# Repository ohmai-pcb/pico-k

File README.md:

<!-- SPDX-License-Identifier: CERN-OHL-P-2.0 -->
<!-- Copyright 2026 The OhmAI contributors -->
# 🌡️ pico-k — RP2350A + MAX31856 Type-K Thermocouple Board

**A 51 × 21 mm Raspberry Pi Pico 2 drop-in board with an integrated 19-bit Type-K thermocouple front end — built end-to-end as the v0.1 dogfood showcase for [OhmAI](https://github.com/ohmai-pcb/ohmai).**

[**Honest Assessment & Grades**](#project-status--honest-assessment) · [**Design effort / AI usage (estimate)**](#design-effort--ai-usage-estimate) · [**Key Specifications**](#key-specifications-verified-against-bombomcsv) · [**On-Board Pin Map**](#on-board-pin-map-rp2350a-verified-against-hardwaregenpinmapyaml) · [**Repo Map & Checks**](#repository-map--running-checks) · [**Exceptions & Waivers**](#exceptions-and-waivers)

| 2D Routed Layout (`docs/layout/routed-2d.png`) | 3D Rendered Board (`docs/layout/routed-3d.png`) |
|---|---|
|  |  |

**Designed with [OhmAI](https://github.com/ohmai-pcb/ohmai).** Rev-A design, pre-fab: ERC and DRC are clean; the board has not been fabricated yet.

---

### What is `pico-k`?

`pico-k` is an open hardware reference project and the **v0.1 dogfood testbed** built to stress-test [OhmAI](https://github.com/ohmai-pcb/ohmai)'s 12-phase hardware engineering workflow, datasheet citation checks, 3-rule BOM sourcing, and independent review gates.

Every artifact in this repository — from requirements (`docs/requirements.md`), safety/compliance analysis (`docs/safety.md`), and page-cited component constraints (`parts/constraints/*.yaml`) to the 6-sheet hierarchical KiCad 9 schematic (`hardware/*.kicad_sch`), 4-layer routed PCB (`hardware/pico-k.kicad_pcb`), multi-source BOM (`bom/bom.csv`), and pre-board bring-up self-test (`test/firmware/bringup_selftest.py`) — was generated and verified through `ohmai` with a human owner reviewing and signing off at each gate.

### ✨ Hardware Highlights

- 🧠 **Raspberry Pi Pico 2 Core (`RP2350A`)** — Dual Cortex-M33 / Hazard3 MCU (`U1`, QFN-60 7×7 mm), **Winbond `W25Q32RVXHJQ`** 4 MB QSPI flash (`U2`, XSON-8 2×3 mm), **Abracon `ABM8-272-T3`** 12 MHz crystal (`Y1`), and internal 1.1 V DVDD buck inductor **MPS `MPL-AT2512-3R3`** (`L1`, 3.3 µH) following the *Hardware Design with RP2350* reference circuit.
- 🌡️ **19-Bit Cold-Junction-Compensated Type-K Front End (`MAX31856MUD+T`)** — Analog Devices `MAX31856` (`U5`, TSSOP-14) on `SPI1` (`GP12`–`GP15` via cuttable jumpers `JP1`–`JP4`; `DRDY` and `FAULT` on `TP11`/`TP12`), paired with top-mounted **Omega `PCC-SMD`** miniature flat-pin Type-K socket clips (`J2`, `J3`) and a differential/common-mode RC input filter (`R12`/`R13` 100 Ω, `C25`/`C26` 10 nF X7R, `C14` 100 nF X7R).
- ⚡ **Buck-Boost 3.3 V Power & Protected USB-C** — **TI `TPS63001DRCR`** (`U3`, VSON-10 3×3 mm) 3.3 V buck-boost regulator with **Murata `DFE201612P-2R2M`** 2.2 µH inductor (`L2`, 2016), 16-pin USB-C receptacle (`J1`), **STMicro `USBLC6-2SC6`** ESD array (`U4`, SOT-23-6), and **onsemi `MBR120VLSFT1G`** (`D1`, SOD-123FL) `VBUS`→`VSYS` Schottky diode.
- 📏 **Drop-In 51 × 21 mm Form Factor with Flat Bottom (`R-02`, `R-07`)** — 4-layer 1.0 mm FR-4 stackup (`F.Cu` / `In1.Cu` solid GND / `In2.Cu` 3V3 / `B.Cu`), single-sided top SMD assembly (`66` fitted parts across `36` BOM rows), and 40-pin Pico-compatible edge pinout (`J4`).

---

## Project Status & Honest Assessment

| Dimension | Grade | Honest Commentary |
|---|---|---|
| **1. End-to-End Autonomy** | **5.5 / 10** | **Human-steered, not hands-off, and not yet physically built.** The workflow produced a complete, rule-checked package from Phase 1 (`requirements`) through Phase 11 (`out/fab/rev-A/`) and Phase 12 pre-board preparation (`test/bringup-plan.md`, `test/firmware/bringup_selftest.py`, `docs/manual.md`). However, getting there required substantial human owner steering, course corrections, and tool fixes along the way (`D-001`–`D-030`, `docs/layout/retro.md`), and the board has **not yet been ordered or bench-tested** (`review:fab` and `review:bringup` remain open). |
| **2. Engineering Complexity / Skill Level** | **4.5 / 10** | **Reference-application complexity.** Electrically, this is a straightforward modification of a Raspberry Pi Pico 2 reference design combining three application circuits (`RP2350A` core, `TPS63001` buck-boost, and `MAX31856` SPI thermocouple front end) — low-to-moderate difficulty for an electronics engineer. Where the workflow added genuine rigor was in quantitative verification (exact datasheet page citations, DC-bias derating math, thermal/loop checks, and verified multi-source BOM alternates). |
| **3. PCB Routing & Layout Quality** | **5.0 / 10** | **DRC-clean (`0` violations, `0` unconnected), but visibly machine-routed.** Fitting 66 top-side SMD parts (including two large `PCC-SMD` thermocouple clips `J2`/`J3`) into 51 × 21 mm via `Freerouting` + scripted pass-completion (`hardware/gen/pcb/handroute.py`) produced meandering autorouter traces rather than clean human layout artistry. Closing the board required owner waivers for 25 short signal hops on the `In2.Cu` (`3V3`) plane (`D-020`/`D-023`, pour remains 1 piece with a 0.91 mm minimum neck), downsizing `C18`/`C27` to `0402` (`D-025`), and accepting stretched decoupler placement (`3.2–11.8 mm`) on several `RP2350A` supplies (`D-030`). Every compromise is listed in [Exceptions and waivers](#exceptions-and-waivers). |

---

## Key Specifications (Verified against `bom/bom.csv`)

| Subsystem | RefDes & MPNs (`bom/bom.csv`) | Reference / Decision |
|---|---|---|
| **MCU & Memory** | `U1` Raspberry Pi `RP2350A` (QFN-60 7×7, `C42411118`), `L1` MPS `MPL-AT2512-3R3` (3.3 µH DVDD buck inductor, `C3224274`), `U2` Winbond `W25Q32RVXHJQ` (4 MB QSPI flash, XSON-8 2×3, `C32246052`), `Y1` Abracon `ABM8-272-T3` (12 MHz crystal, SMD3225-4P, `C20625731`) with `C23`/`C24` 15 pF C0G (`C1548`) & `R3` 1 kΩ (`C11702`) | [`parts/constraints/RP2350A.yaml`](parts/constraints/RP2350A.yaml), `D-001`, `D-006`, `D-009` |
| **Thermocouple Front End** | `U5` Analog Devices `MAX31856MUD+T` (TSSOP-14, `C2653162`), `J2`/`J3` Omega `PCC-SMD` (2 × SMT flat-pin socket clips), `R12`/`R13` 100 Ω series (`0402WGF1000TCE`, `C25076`), `C25`/`C26` 10 nF 50 V X7R CM (`CL05B103KB5NNNC`, `C15195`), `C14` 100 nF 16 V X7R diff (`CL05B104KO5NNNC`, `C1525`), `C12`/`C13` 100 nF `AVDD`/`DVDD` decouplers | [`parts/constraints/MAX31856MUD+T.yaml`](parts/constraints/MAX31856MUD+T.yaml), `R-03`, `R-04`, `R-07`, `D-001`, `D-004` |
| **Power & USB Stage** | `U3` TI `TPS63001DRCR` (3.3 V buck-boost, VSON-10 3×3, `C28060`), `L2` Murata `DFE201612P-2R2M` (2.2 µH, 2016, `C79317`), `C20` Samsung `CL21A106KAYNNNE` (10 µF 25 V X5R, 0805, `C15850`), `C21`/`C22`/`C31` 3 × 10 µF 25 V X5R (`CL10A106MA8NRNC`, 0603, `C96446`), `J1` SHOU HAN `TYPE-C 16PIN 2MD(073)` (`C2765186`), `U4` STMicro `USBLC6-2SC6` (SOT-23-6 USB ESD, `C7519`), `D1` onsemi `MBR120VLSFT1G` (SOD-123FL Schottky, `C223608`) | [`parts/constraints/TPS63001DRCR.yaml`](parts/constraints/TPS63001DRCR.yaml), `D-004`, `D-006`, `D-030` |
| **Housekeeping & UI** | `SW1` XKB `TS-1187A-B-A-B` (`BOOTSEL` button, SMD 5.1×5.1, `C318884`) via `R4` 1 kΩ, `D2` KENTO `KT-0805G` (0805 green LED on `GP25`, `C2297`) via `R22` 470 Ω (`C25117`), `Q1` Diodes Inc. `DMG1012T-7` (SOT-523 N-MOSFET on `VSYS_SENSE`, `C20512`) with `R19` 20 kΩ / `R9` 10 kΩ divider | [`hardware/led_boot_adc.kicad_sch`](hardware/led_boot_adc.kicad_sch), `D-006`, `D-007` |
| **PCB Stackup & Form Factor** | **51.0 × 21.0 mm** (`R-02`), 4-layer 1.0 mm FR-4 (`F.Cu` / `In1.Cu` solid GND / `In2.Cu` 3V3 / `B.Cu`), ENIG (JLCPCB `JLC04101H-7628`), top-side SMD assembly (`R-07`), EU target market (`D-003`) | [`docs/requirements.md`](docs/requirements.md), `D-003`, `D-006`, `D-017` |

---

## On-Board Pin Map (`RP2350A`, verified against `hardware/gen/pinmap.yaml`)

| Signal / GPIO | Pin / Net Routing (`pinmap.yaml`) | On-Board Function |
|---|---|---|
| `GP12` (`SPI1_RX`) | `U1.16` / `J4.16` / `JP1` → `U5.11` (`TC_SDO`) | `MAX31856` `SDO` (SPI1 MISO via cuttable jumper `JP1`) |
| `GP13` (`SPI1_CSn`) | `U1.17` / `J4.17` / `JP2` → `U5.9` (`TC_CS`) | `MAX31856` `CS` (SPI1 CSN via `JP2`, 10 kΩ pull-up `R7` to `3V3`) |
| `GP14` (`SPI1_SCK`) | `U1.18` / `J4.19` / `JP3` → `U5.10` (`TC_SCK`) | `MAX31856` `SCLK` (SPI1 SCK via `JP3`) |
| `GP15` (`SPI1_TX`) | `U1.19` / `J4.20` / `JP4` → `U5.12` (`TC_SDI`) | `MAX31856` `SDI` (SPI1 MOSI via `JP4`) |
| `TC_DRDY` | `U5.7` / `TP11.1` (DNF 10 kΩ pull-up `R23`) | `MAX31856` active-low data-ready test pad `TP11` (optional jumper to `GP6`) |
| `TC_FAULT` | `U5.13` / `TP12.1` (DNF 10 kΩ pull-up `R24`) | `MAX31856` active-low fault test pad `TP12` (optional jumper to `GP7`) |
| `GP23` (`SMPS_PS`) | `U1.35` / `TP4.1` / `U3.7` (100 kΩ pull-down `R16`) | `TPS63001` `PS/SYNC` power-save mode control (`LOW` = PFM, `HIGH` = PWM) |
| `GP24` (`VBUS_SENSE`) | `U1.36` (`R18` 5.6 kΩ / `R8` 10 kΩ divider) | USB `VBUS` presence sense |
| `GP25` | `U1.37` / `R22.1` / `D2` / `TP5.1` | User green LED `D2` (`KT-0805G`) active-high via `R22` (470 Ω) |
| `GP29` (`ADC3`) | `U1.43` (`VSYS_SENSE`) | `VSYS` ÷ 3 sense via `Q1` (`DMG1012T-7` N-MOSFET) + `R19` 20 kΩ / `R9` 10 kΩ |
| `BOOTSEL` | `SW1.1` / `TP6.1` / `U2.1` (`QSPI_SS` via `R4` 1 kΩ) | `BOOTSEL` tactile switch `SW1` (`TS-1187A-B-A-B`) active-low on `QSPI_SS` |
| `3V3_EN` / `RUN` | `J4.37` (`U3.6`, `R15` 100 kΩ to `VSYS`) / `J4.30` (`U1.26`) | `TPS63001` enable and `RP2350A` active-low hardware reset |

---

## Repository Map & Running Checks

- **Project status & logs:** [`STATUS.md`](STATUS.md), [`docs/decisions.md`](docs/decisions.md), [`docs/layout/retro.md`](docs/layout/retro.md)
- **Specs & compliance:** [`docs/requirements.md`](docs/requirements.md), [`docs/architecture.md`](docs/architecture.md), [`docs/safety.md`](docs/safety.md), [`docs/manual.md`](docs/manual.md)
- **Parts, constraints & datasheets:** [`parts/selection.md`](parts/selection.md), [`parts/constraints/`](parts/constraints/), [`datasheets/manifest.yaml`](datasheets/manifest.yaml), [`bom/bom.csv`](bom/bom.csv)
- **KiCad design & generators:** [`hardware/`](hardware/) (`pico-k.kicad_pro`, root `pico-k.kicad_sch` + 6 hierarchical subsheets `power_usb`, `regulator`, `mcu_core`, `thermocouple`, `led_boot_adc`, `edge`, `pico-k.kicad_pcb`, `hardware/gen/`)
- **Reviews & bring-up:** [`reviews/`](reviews/), [`test/bringup-plan.md`](test/bringup-plan.md), [`test/firmware/bringup_selftest.py`](test/firmware/bringup_selftest.py)

```bash
pip install -e <ohmai-checkout>/cli
ohmai status
ohmai datasheets fetch && ohmai datasheets check
ohmai check constraints --gate
ohmai check schematic --gate
ohmai check layout --gate
ohmai check bom --gate
```

## Exceptions and waivers

These are pico-k-only decisions by the owner. They are **not OhmAI defaults**: the OhmAI template, skill and
gate configuration are unchanged, and another project starts without any of them. Details and reasons are in
[`docs/decisions.md`](docs/decisions.md) under each ID.

- **D-009 – L1 inductor deviation.** L1 is an MPL-AT2512-3R3, not the RP2350 reference inductor. This is a
  documented rev-A deviation. Both orientations are built, and the external 1.1 V DVDD supply stays possible as a
  fallback (JP5/JP6 solder jumpers, feed into TP7).
- **D-010 – USB inrush deviation.** At attach, pico-k draws more charge from VBUS than USB 2.0 allows, and C19
  alone is above the USB capacitance limit. This is accepted for rev-A, with a VBUS droop test in bring-up and a load
  switch plan for rev-B if it fails. No USB compliance claim or USB logo while this stands.
- **D-016 – Schematic review independence waiver.** For the schematic gate, the owner accepted Reviewer-A as the
  reviewer at independence level 3 instead of the configured level 2, for that gate and that files_hash only.
- **D-017 – Mechanical deviations from the Pico 2.** No mounting holes. The four end pins (1, 20, 21, 40) keep
  their positions but have no castellated half-hole, because JLC's castellation edge rules can't be met there in
  the Pico 2 outline. When the board is soldered flat onto a carrier, those four joints can't be inspected.
  Also accepted: the PCC-SMD slot non-plated, the clip tab depth on a 1.0 mm board (fit checked at bring-up), the
  test-point mapping, and the small layout deviations listed under P8-6.
- **D-020 + D-023 – Signals on the In2 (3V3) plane layer.** Normally In2 is a solid 3V3 plane. Here, signals may
  run on In2, including longer runs (D-023). The rules: the 3V3 pour stays one connected piece, pour necks are at
  least 0.5 mm wide (at least 0.8 mm near U1 and the decouplers), In1 (GND) stays solid with no signals, and USB,
  GND and 3V3 never route as tracks on In2.
- **D-021 – Placement rework around U1, and JP5/JP6 on the bottom.** The placement around the RP2350 was reworked
  for escape channels (flash moved, decoupler columns spaced out). JP5/JP6 are bare-copper solder jumpers on the
  bottom side. That needs the owner's reading of R-07 (bottom flat, no parts), and is accepted for now unless the
  owner objects (D-022).
- **D-022 – Scripted hand-routing.** The connections the autorouter left open are routed by a scripted,
  replayable step on top of a frozen autorouter result, instead of by the autorouter alone.
- **D-024 / D-025 – Right passive column shift and a BOM change.** The cap/resistor column right of U1 moved about
  0.5 mm outward. To make room, C18 and C27 changed from 0603 (`CL10A475KO8NNNC`) to 0402 4.7 µF 25 V X5R parts (Taiyo Yuden `TDK105CBJ475MV-F`, LCSC `C22385335`, JLC extended — note: `TDK105CBJ475MV-F` is Taiyo Yuden's actual MPN per `bom/bom.csv` and `datasheets/TDK105CBJ475MV-F.pdf`, where `T` = 25 V, `DK` = series code, `105` = 1005 metric / 0402).
  At 3.3 V their effective capacitance is about 16 % lower than the 0603's (about 2.7 µF typical instead of 3.2 µF,
  DC-bias derating). The owner accepted that and the extended-part fee.
- **D-026 – Q1 placement and the last links.** Q1 could not move next to U1 (no room). It stays on the west edge,
  with R19/R9 moved next to it (electrically identical). VSYS_SENSE and VBUS_SENSE are therefore long hand routes.
  Two silkscreen overlaps were cleared by small part nudges instead of waivers.
- **D-027 – DVDD decoupler placement.** C9 sits directly under U1 pin 23 (DVDD) with a short trace and no via. C28
  moved down to make room. The crystal parts stay where they were.
- **D-028 – Layout review independence waiver.** For the layout gate, the owner accepted Reviewer-A as the reviewer at
  independence level 3 instead of level 2, for that gate and the reviewed `files_hash` values (`c71de844…` and D-030 `a0379e72…`) only. A level 1/2 cloud reviewer was
  possible, but the owner chose Reviewer-A.
- **D-029 – TPS63001 input capacitor deferral (superseded by D-030).** With the pre-D-030 3015 inductor and 1206 C20, four placement/reroute attempts could not move C20 to U3 VIN and close routing at 51 × 21 mm; superseded by D-030, which resolves L1 on the 51 × 21 mm board. The approved In2 exceptions (VBUS_SENSE hop, SMPS_PS stub) were not needed and are not used on the board.
- **D-030 – BOM and layout rework for TPS63001 and ADC_AVDD at 51 × 21 mm.** L2 changed to Murata DFE201612P-2R2M (2016, JLC extended part C79317, custom footprint `pico-k:L_Murata_DFE201612P` with an all-layer under-coil keepout), C20 changed to Samsung CL21A106KAYNNNE (0805 10 µF 25 V X5R, ~5.8 µF typical / ~5.0 µF worst-case at 5 V ≥ 4.7 µF SLVS520C minimum), and C32 (100 nF 0402 CL05B104KO5NNNC) was added on ADC_AVDD at U1 pin 44 alongside C27. On the routed 51 × 21 mm board (`5d80779`, 0 DRC violations, 0 unconnected items), C20.1 reaches U3.5 [VIN] in 1.65 mm center-to-center (0.62 mm pad-edge gap, 1.55 mm routed on F.Cu at 0.30 mm width with 0 vias), resolving Reviewer-A L1; L2 has zero copper across all layers in its under-coil keepout and 0.25 mm switch traces (resolving L6 and L13); C32 decouples U1.44 (resolving L5 and Q3). The In2.Cu 3V3 pour remains 1 piece (772.70 mm², narrowest neck 0.91 mm), In1.Cu has 0 signal tracks, and only short signal hops (`DVDD`, `/ADC_AVDD`, `/ADC_VREF`, `/GP8`–`/GP10`, `/GP12`–`/GP14`, `/GP18`–`/GP22`, `/GP25`, `/QSPI_SD1`, `/QSPI_SD2`, `/QSPI_SS`, `/VSYS_SENSE`, `Net-(D1-A)`, `Net-(J4-Pad30)`) use In2.Cu under D-020/D-023 (neither the VBUS_SENSE In2 hop nor the SMPS_PS In2 stub was used). The remaining 51 × 21 mm placement/density trade-offs (Reviewer-A L2–L4 and L7–L12) were accepted by the owner in `reviews/layout/resolutions.md`.

---

## Design effort / AI usage (estimate)

Figures below are an **estimate** of AI-agent design effort from the project's commit log and recorded decisions. They are not billed usage, and request or token counts are not available for the full design period. Toolchain development that was not specific to this board is excluded.

| | |
|---|---|
| Wall-clock span | 15–26 October 2026 (12 calendar days) |
| Active days | 7 days with commits (6 in the pre-publication history, plus a documentation commit on 26 October). No commits 18–22 October. |
| Agent sessions | 10 (9 design sessions in the pre-publication history, plus the 26 October documentation commit) |
| Git commits | 182 in the pre-publication history (176 non-merge); later condensed to 2 commits on the published default branch |
| Approximate usage | About 33 hours of elapsed time across the 9 design sessions (35 distinct hours that contain a commit), plus one later documentation commit. Lower bound. |
| Human decisions | 31 recorded design decisions (D-000–D-030), plus independent reviews of constraints, schematic, layout (2 rounds), and BOM (2 rounds) |

Freerouting 2.1.0 and 2.2.4 were used; after those runs plateaued, remaining nets were finished with a scripted hand-router. In the pre-publication history, 13 commits mention Freerouting and 33 mention hand routing.

Method: a session is a cluster of commits with no gap longer than 3 hours. Session hours are the elapsed time from the first to the last commit in each cluster. That is a lower bound: it omits agent work that left no commit, and the independent reviewer's time. Chat-turn and token totals were not available for the whole design period.

---

## License

pico-k is licensed under the CERN Open Hardware Licence Version 2 - Permissive (CERN-OHL-P-2.0). See [LICENSE](LICENSE) and [NOTICE](NOTICE).

The [OhmAI](https://github.com/ohmai-pcb/ohmai) tool used to design this board remains licensed under Apache-2.0.

Designed with [OhmAI](https://github.com/ohmai-pcb/ohmai).

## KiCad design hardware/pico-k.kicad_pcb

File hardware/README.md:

# hardware/

KiCad 9 project: `pico-k.kicad_pro`, `.kicad_sch` (root sheet), `.kicad_pcb`.

- Phase 7: the root sheet holds only hierarchical sheets, **one functional block per sheet**
  (`power_in.kicad_sch`, `regulator.kicad_sch`, ...).
- Symbols and footprints come from KiCad's official libraries or `lib/` (project library, reviewed
  in a PR). Never generate them.
- Put each part's MPN in a symbol field named `MPN` so checks can match `parts/constraints/`.
- Phase 8: fab design rules go in `pico-k.kicad_dru` (fab capabilities plus creepage from `docs/safety.md`).
- `release.kibot.yaml` holds the KiBot outputs for tagged releases (CI only).

## Phase 7 notes (2026-10-15, D-012)
- Libraries: official KiCad **9.0.9.1** symbols and footprints, pinned in `ohmai.yaml` (`kicad.libraries`), installed
  with `ohmai kicad-libs install` and referenced through the project tables `sym-lib-table` / `fp-lib-table`
  (`${OHMAI_KICAD_SYMBOLS}` / `${OHMAI_KICAD_FOOTPRINTS}`, written by `ohmai kicad-libs tables`). Symbols are embedded
  verbatim; ERC reports no `lib_symbol_issues`.
- Source of the sheets: `gen/layout/_root.yaml` + one yaml per block (power_usb, mcu_core, regulator, thermocouple,
  edge, led_boot_adc), drawn by `ohmai schematic build` in datasheet-figure style (real wires; hierarchical labels
  only between blocks). Each yaml names its reference figure. Do not hand-edit the .kicad_sch files while the
  generator is the source; change the yaml and rebuild. The old `gen/*.py` draft generator is retired.
- Library pins that differ from the datasheet are mapped in `../parts/symbol-maps/` (the reviewed constraints are
  not edited).
- Footprints left empty on purpose (phase 8, STATUS P7-10): J1, U1, U2, U3, U4, U5, L1, L2, Q1, J2/J3 (Omega PCC-SMD
  custom footprint), J4.
- VREG_PGND is a wired net (no power symbol): C16/C29/C17 returns at U1 pin 47, joined to GND only through NT1.

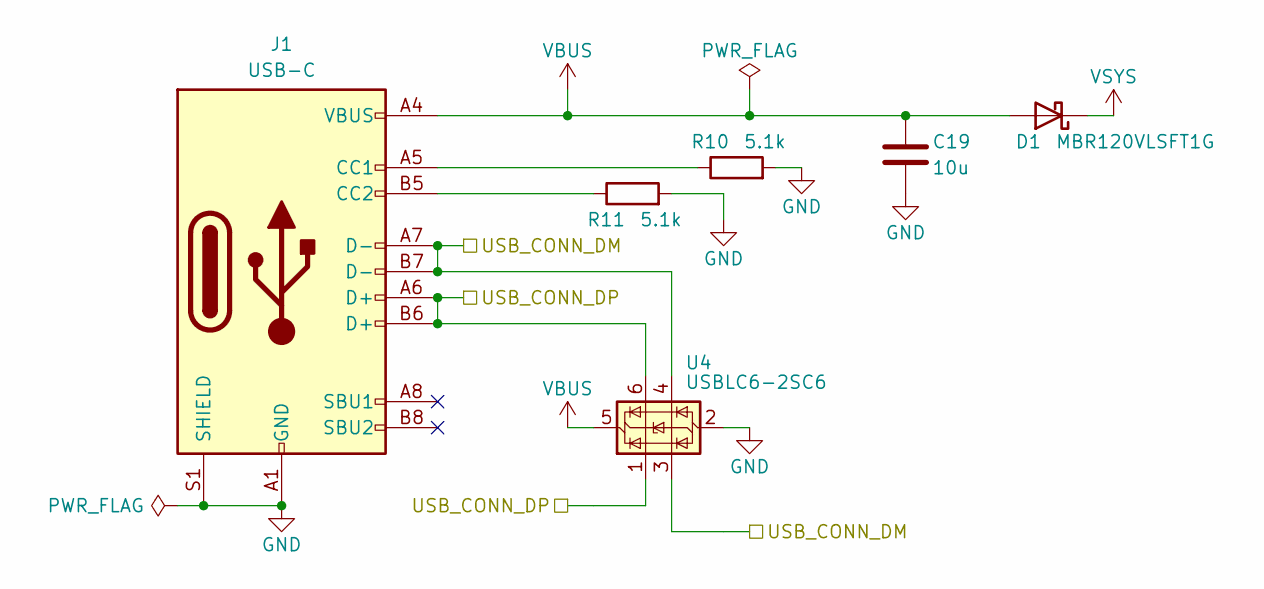
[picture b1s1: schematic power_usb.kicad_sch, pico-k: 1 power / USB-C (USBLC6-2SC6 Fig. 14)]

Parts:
C19: 10u; C_0603_1608Metric; MPN CL10A106MA8NRNC
D1: MBR120VLSFT1G; D_SOD-123F; MPN MBR120VLSFT1G
J1: USB-C; USB_C_Receptacle_ShouHan_TYPE-C-16PIN-2MD-073; MPN TYPE-C 16PIN 2MD(073)
R10, R11: 5.1k; R_0402_1005Metric; MPN 0402WGF5101TCE
U4: USBLC6-2SC6; SOT-23-6; MPN USBLC6-2SC6

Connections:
/USB_CONN_DM: J1.A7 (D-), J1.B7 (D-), U4.3 (I/O2), U4.4 (I/O2); also elsewhere on the board
/USB_CONN_DP: J1.A6 (D+), J1.B6 (D+), U4.1 (I/O1), U4.6 (I/O1); also elsewhere on the board
GND: C19.2, J1.A1 (GND), J1.A12 (GND), J1.B1 (GND), J1.B12 (GND), J1.S1 (SHIELD), R10.2, R11.2, U4.2 (GND); also elsewhere on the board
unnamed: J1.A5 (CC1), R10.1
unnamed: J1.B5 (CC2), R11.1
VBUS: C19.1, D1.2 (A), J1.A4 (VBUS), J1.A9 (VBUS), J1.B4 (VBUS), J1.B9 (VBUS), U4.5 (VBUS); also elsewhere on the board
VSYS: D1.1 (K); also elsewhere on the board

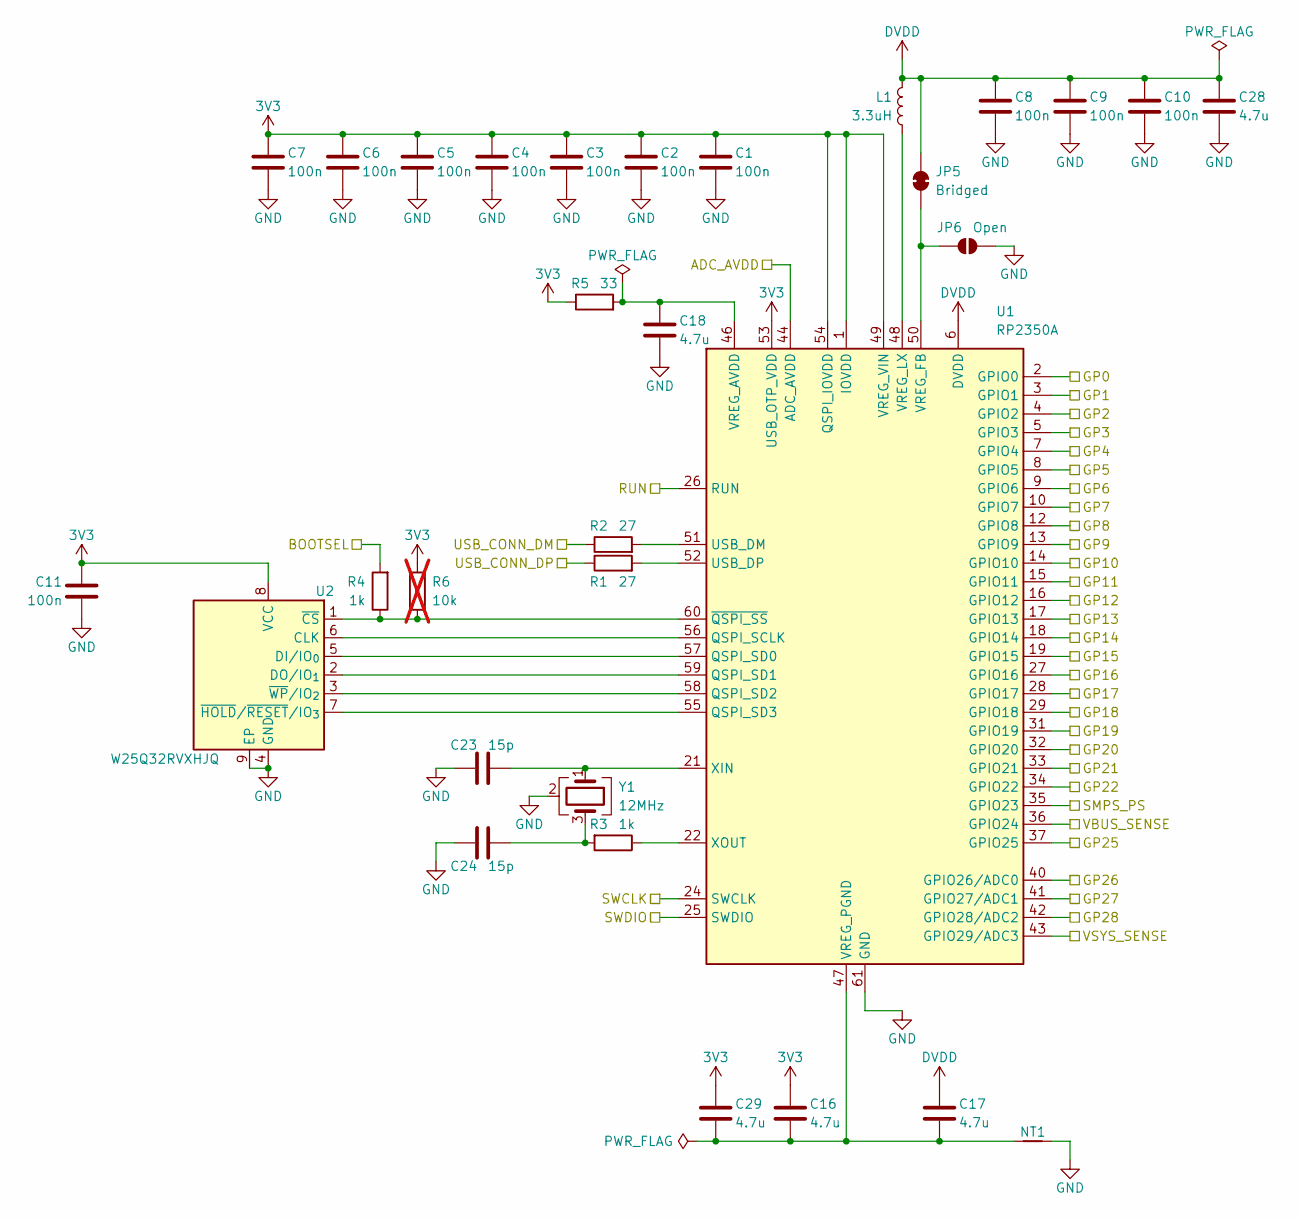
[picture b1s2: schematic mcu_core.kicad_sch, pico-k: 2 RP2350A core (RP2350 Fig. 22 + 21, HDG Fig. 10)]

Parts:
C1, C2, C3, C4, C5, C6, C7, C8, C9, C10, C11: 100n; C_0402_1005Metric; MPN CL05B104KO5NNNC
C16, C17, C28, C29: 4.7u; C_0603_1608Metric; MPN CL10A475KO8NNNC
C18: 4.7u; C_0402_1005Metric; MPN TDK105CBJ475MV-F
C23, C24: 15p; C_0402_1005Metric; MPN 0402CG150J500NT
JP5: Bridged; SolderJumper-2_P1.3mm_Bridged_RoundedPad1.0x1.5mm
JP6: Open; SolderJumper-2_P1.3mm_Open_RoundedPad1.0x1.5mm
L1: 3.3uH; L_MPS_MPL-AT2512; MPN MPL-AT2512-3R3
NT1: NetTie_2; NetTie-2_SMD_Pad0.5mm
R1, R2: 27; R_0402_1005Metric; MPN 0402WGF270JTCE
R3, R4: 1k; R_0402_1005Metric; MPN 0402WGF1001TCE
R5: 33; R_0402_1005Metric; MPN 0402WGF330JTCE
R6: 10k; R_0402_1005Metric; MPN 0402WGF1002TCE; not fitted
U1: RP2350A; QFN-60-1EP_7x7mm_P0.4mm_EP3.4x3.4mm_ThermalVias; MPN RP2350A
U2: W25Q32RVXHJQ; Winbond_USON-8-1EP_3x2mm_P0.5mm_EP0.2x1.6mm; MPN W25Q32RVXHJQ
Y1: 12MHz; Crystal_SMD_3225-4Pin_3.2x2.5mm; MPN ABM8-272-T3

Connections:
3V3: C1.1, C2.1, C3.1, C4.1, C5.1, C6.1, C7.1, C11.1, C16.1, C29.1, R5.1, R6.2, U1.1 (IOVDD), U1.11 (IOVDD), U1.20 (IOVDD), U1.30 (IOVDD), U1.38 (IOVDD), U1.45 (IOVDD), U1.49 (VREG_VIN), U1.53 (USB_OTP_VDD), U1.54 (QSPI_IOVDD), U2.8 (VCC); also elsewhere on the board
/ADC_AVDD: U1.44 (ADC_AVDD); also elsewhere on the board
/BOOTSEL: R4.2; also elsewhere on the board
/GP0: U1.2 (GPIO0); also elsewhere on the board
/GP1: U1.3 (GPIO1); also elsewhere on the board
/GP2: U1.4 (GPIO2); also elsewhere on the board
/GP3: U1.5 (GPIO3); also elsewhere on the board
/GP4: U1.7 (GPIO4); also elsewhere on the board
/GP5: U1.8 (GPIO5); also elsewhere on the board
/GP6: U1.9 (GPIO6); also elsewhere on the board
/GP7: U1.10 (GPIO7); also elsewhere on the board
/GP8: U1.12 (GPIO8); also elsewhere on the board
/GP9: U1.13 (GPIO9); also elsewhere on the board
/GP10: U1.14 (GPIO10); also elsewhere on the board
/GP11: U1.15 (GPIO11); also elsewhere on the board
/GP12: U1.16 (GPIO12); also elsewhere on the board
/GP13: U1.17 (GPIO13); also elsewhere on the board
/GP14: U1.18 (GPIO14); also elsewhere on the board
/GP15: U1.19 (GPIO15); also elsewhere on the board
/GP16: U1.27 (GPIO16); also elsewhere on the board
/GP17: U1.28 (GPIO17); also elsewhere on the board
/GP18: U1.29 (GPIO18); also elsewhere on the board
/GP19: U1.31 (GPIO19); also elsewhere on the board
/GP20: U1.32 (GPIO20); also elsewhere on the board
/GP21: U1.33 (GPIO21); also elsewhere on the board
/GP22: U1.34 (GPIO22); also elsewhere on the board
/GP25: U1.37 (GPIO25); also elsewhere on the board
/GP26: U1.40 (GPIO26/ADC0); also elsewhere on the board
/GP27: U1.41 (GPIO27/ADC1); also elsewhere on the board
/GP28: U1.42 (GPIO28/ADC2); also elsewhere on the board
/RUN: U1.26 (RUN); also elsewhere on the board
/SMPS_PS: U1.35 (GPIO23); also elsewhere on the board
/SWCLK: U1.24 (SWCLK); also elsewhere on the board
/SWDIO: U1.25 (SWDIO); also elsewhere on the board
/USB_CONN_DM: R2.1; also elsewhere on the board
/USB_CONN_DP: R1.1; also elsewhere on the board
/VBUS_SENSE: U1.36 (GPIO24); also elsewhere on the board
/VSYS_SENSE: U1.43 (GPIO29/ADC3); also elsewhere on the board
DVDD: C8.1, C9.1, C10.1, C17.1, C28.1, JP5.2 (B), L1.2, U1.6 (DVDD), U1.23 (DVDD), U1.39 (DVDD); also elsewhere on the board
GND: C1.2, C2.2, C3.2, C4.2, C5.2, C6.2, C7.2, C8.2, C9.2, C10.2, C11.2, C18.2, C23.2, C24.2, C28.2, JP6.2 (B), NT1.2, U1.61 (GND), U2.4 (GND), U2.9 (EP), Y1.2 (G), Y1.4 (G); also elsewhere on the board
unnamed: C24.1, R3.2, Y1.3
unnamed: JP5.1 (A), JP6.1 (A), U1.50 (VREG_FB)
unnamed: U1.56 (QSPI_SCLK), U2.6 (CLK)
unnamed: U1.57 (QSPI_SD0), U2.5 (DI/IO_{0})
unnamed: U1.59 (QSPI_SD1), U2.2 (DO/IO_{1})
unnamed: U1.58 (QSPI_SD2), U2.3 (~WP/IO_{2})
unnamed: U1.55 (QSPI_SD3), U2.7 (~HOLD/~RESET/IO_{3})
unnamed: R2.2, U1.51 (USB_DM)
unnamed: R1.2, U1.52 (USB_DP)
unnamed: C18.1, R5.2, U1.46 (VREG_AVDD)
unnamed: L1.1, U1.48 (VREG_LX)
unnamed: C16.2, C17.2, C29.2, NT1.1, U1.47 (VREG_PGND)
unnamed: C23.1, U1.21 (XIN), Y1.1
unnamed: R3.1, U1.22 (XOUT)
unnamed: R4.1, R6.1, U1.60 (~QSPI_SS), U2.1 (~CS)

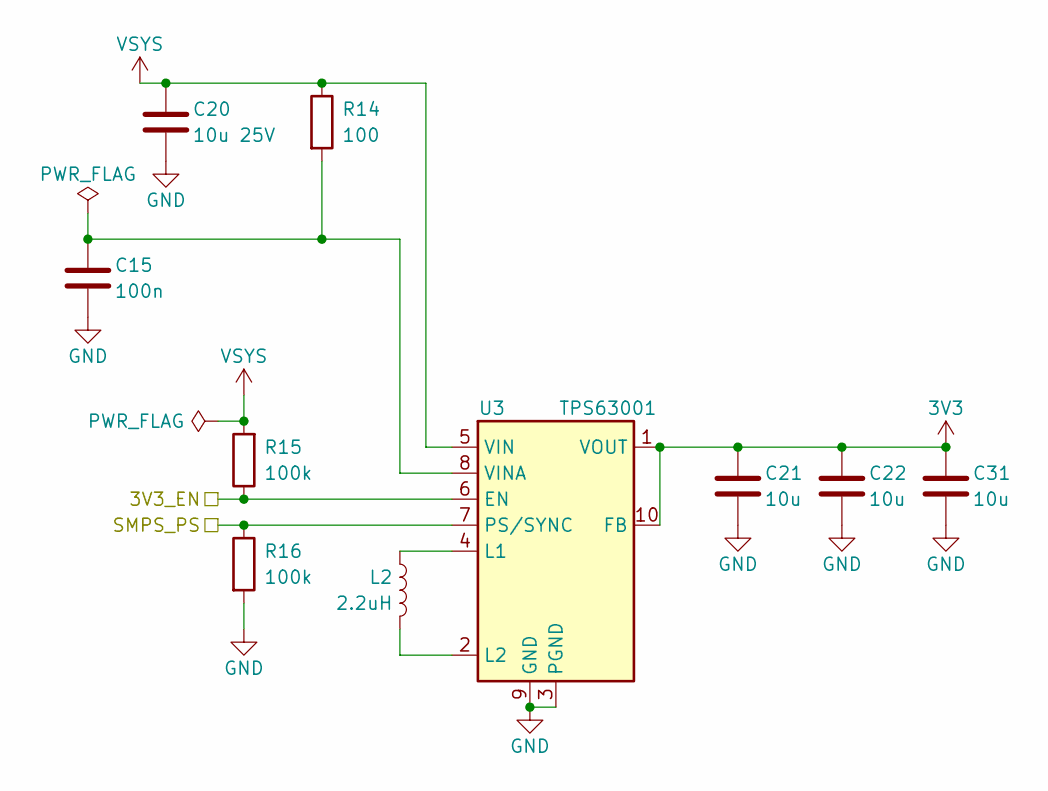
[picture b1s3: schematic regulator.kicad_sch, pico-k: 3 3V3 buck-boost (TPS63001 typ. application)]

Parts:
C15: 100n; C_0402_1005Metric; MPN CL05B104KO5NNNC
C20: 10u 25V; C_0805_2012Metric; MPN CL21A106KAYNNNE
C21, C22, C31: 10u; C_0603_1608Metric; MPN CL10A106MA8NRNC
L2: 2.2uH; L_Murata_DFE201612P; MPN DFE201612P-2R2M
R14: 100; R_0402_1005Metric; MPN 0402WGF1000TCE
R15, R16: 100k; R_0402_1005Metric; MPN 0402WGF1003TCE
U3: TPS63001; Texas_DRC0010J_ThermalVias; MPN TPS63001DRCR

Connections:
3V3: C21.1, C22.1, C31.1, U3.1 (VOUT), U3.10 (FB); also elsewhere on the board
/3V3_EN: R15.1, U3.6 (EN); also elsewhere on the board
/SMPS_PS: R16.1, U3.7 (PS/SYNC); also elsewhere on the board
GND: C15.2, C20.2, C21.2, C22.2, C31.2, R16.2, U3.3 (PGND), U3.9 (GND), U3.11 (PGND); also elsewhere on the board
unnamed: L2.1, U3.4 (L1)
unnamed: L2.2, U3.2 (L2)
unnamed: C15.1, R14.2, U3.8 (VINA)
VSYS: C20.1, R14.1, R15.2, U3.5 (VIN); also elsewhere on the board

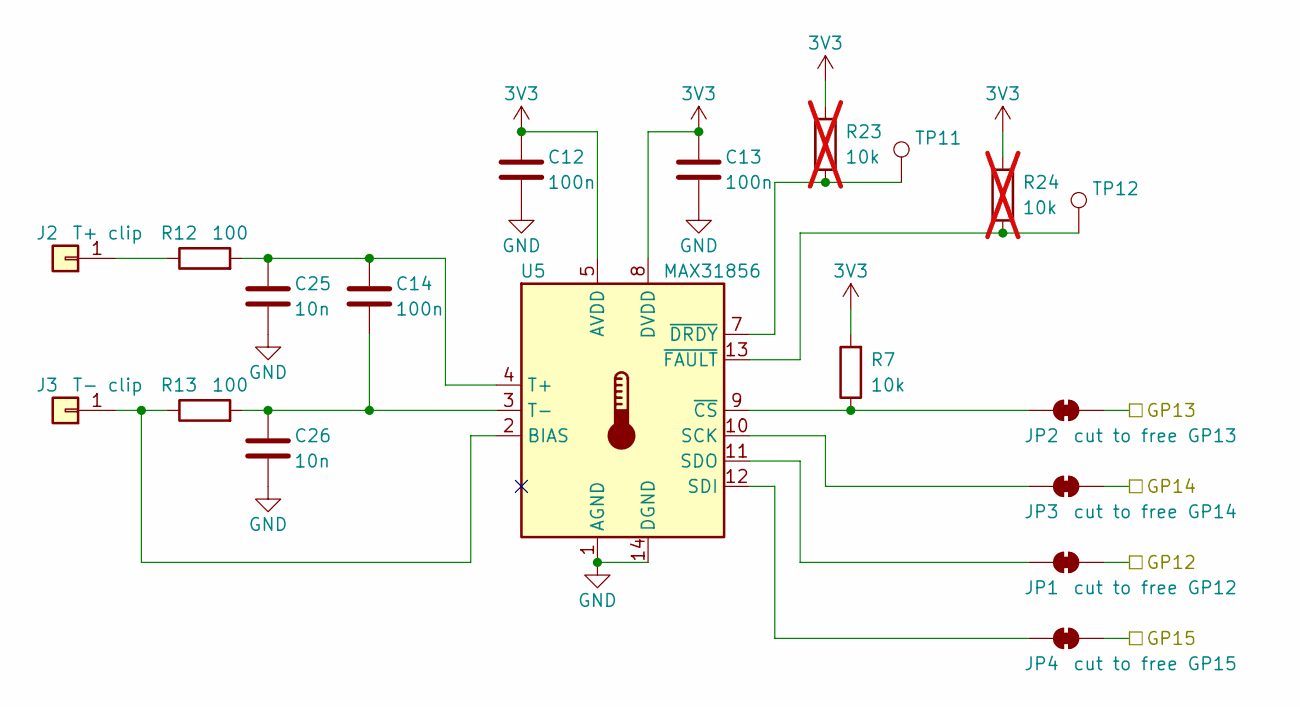
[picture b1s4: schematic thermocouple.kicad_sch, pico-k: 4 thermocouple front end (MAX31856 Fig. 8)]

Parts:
C12, C13, C14: 100n; C_0402_1005Metric; MPN CL05B104KO5NNNC
C25, C26: 10n; C_0402_1005Metric; MPN CL05B103KB5NNNC
J2: T+ clip; Omega_PCC-SMD_Clip_R; MPN PCC-SMD
J3: T- clip; Omega_PCC-SMD_Clip_L; MPN PCC-SMD
JP1: cut to free GP12; SolderJumper-2_P1.3mm_Bridged_RoundedPad1.0x1.5mm
JP2: cut to free GP13; SolderJumper-2_P1.3mm_Bridged_RoundedPad1.0x1.5mm
JP3: cut to free GP14; SolderJumper-2_P1.3mm_Bridged_RoundedPad1.0x1.5mm
JP4: cut to free GP15; SolderJumper-2_P1.3mm_Bridged_RoundedPad1.0x1.5mm
R7: 10k; R_0402_1005Metric; MPN 0402WGF1002TCE
R12, R13: 100; R_0402_1005Metric; MPN 0402WGF1000TCE
R23, R24: 10k; R_0402_1005Metric; MPN 0402WGF1002TCE; not fitted
TP11, TP12: TestPoint; TestPoint_Pico2_1.5x1.5mm
U5: MAX31856; TSSOP-14_4.4x5mm_P0.65mm; MPN MAX31856MUD+T

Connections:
3V3: C12.1, C13.1, R7.2, R23.2, R24.2, U5.5 (AVDD), U5.8 (DVDD); also elsewhere on the board
/GP12: JP1.1 (A); also elsewhere on the board
/GP13: JP2.1 (A); also elsewhere on the board
/GP14: JP3.1 (A); also elsewhere on the board
/GP15: JP4.1 (A); also elsewhere on the board
GND: C12.2, C13.2, C25.2, C26.2, U5.1 (AGND), U5.14 (DGND); also elsewhere on the board
unnamed: J2.1, R12.1
unnamed: J3.1, R13.1, U5.2 (BIAS)
unnamed: JP1.2 (B), U5.11 (SDO)
unnamed: JP2.2 (B), R7.1, U5.9 (~CS)
unnamed: JP3.2 (B), U5.10 (SCK)
unnamed: JP4.2 (B), U5.12 (SDI)
unnamed: C14.1, C25.1, R12.2, U5.4 (T+)
unnamed: C14.2, C26.1, R13.2, U5.3 (T-)
unnamed: R23.1, TP11.1, U5.7 (~DRDY)
unnamed: R24.1, TP12.1, U5.13 (~FAULT)

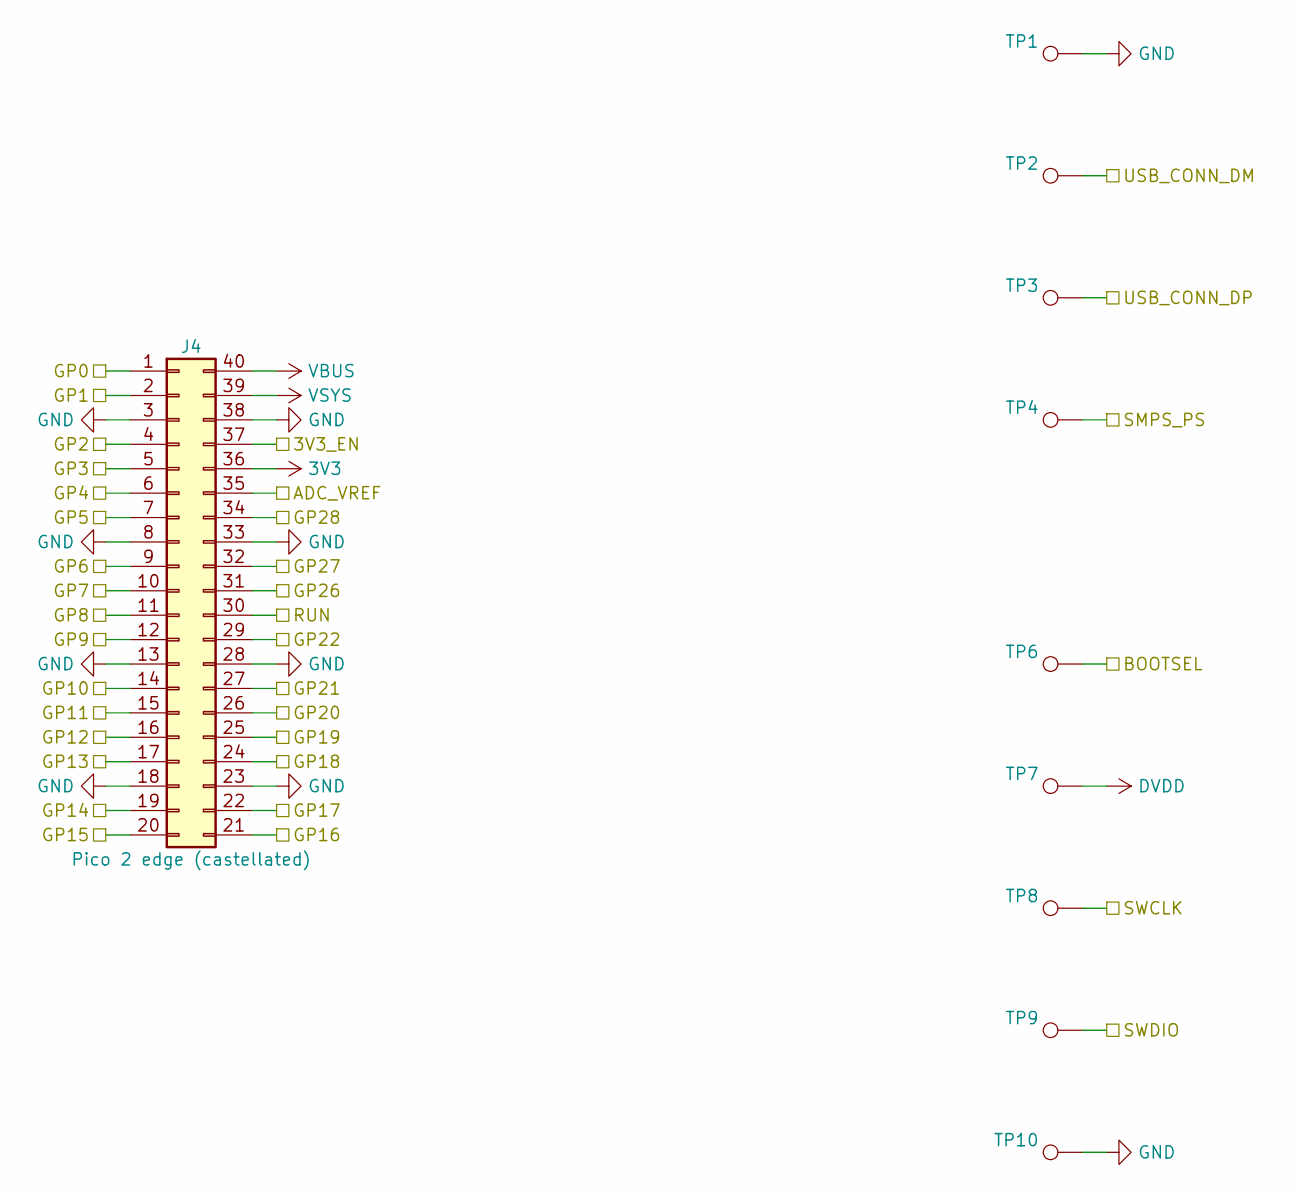
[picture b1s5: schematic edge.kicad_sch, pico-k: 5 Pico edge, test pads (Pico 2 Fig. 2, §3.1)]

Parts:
J4: Pico 2 edge (castellated); RaspberryPi_Pico2_Edge_Castellated_2x20
TP1, TP2, TP3, TP4, TP6, TP7, TP8, TP9, TP10: TestPoint; TestPoint_Pico2_1.5x1.5mm

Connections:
3V3: J4.36; also elsewhere on the board
/3V3_EN: J4.37; also elsewhere on the board
/ADC_VREF: J4.35; also elsewhere on the board
/BOOTSEL: TP6.1; also elsewhere on the board
/GP0: J4.1; also elsewhere on the board
/GP1: J4.2; also elsewhere on the board
/GP2: J4.4; also elsewhere on the board
/GP3: J4.5; also elsewhere on the board
/GP4: J4.6; also elsewhere on the board
/GP5: J4.7; also elsewhere on the board
/GP6: J4.9; also elsewhere on the board
/GP7: J4.10; also elsewhere on the board
/GP8: J4.11; also elsewhere on the board
/GP9: J4.12; also elsewhere on the board
/GP10: J4.14; also elsewhere on the board
/GP11: J4.15; also elsewhere on the board
/GP12: J4.16; also elsewhere on the board
/GP13: J4.17; also elsewhere on the board
/GP14: J4.19; also elsewhere on the board
/GP15: J4.20; also elsewhere on the board
/GP16: J4.21; also elsewhere on the board
/GP17: J4.22; also elsewhere on the board
/GP18: J4.24; also elsewhere on the board
/GP19: J4.25; also elsewhere on the board
/GP20: J4.26; also elsewhere on the board
/GP21: J4.27; also elsewhere on the board
/GP22: J4.29; also elsewhere on the board
/GP26: J4.31; also elsewhere on the board
/GP27: J4.32; also elsewhere on the board
/GP28: J4.34; also elsewhere on the board
/RUN: J4.30; also elsewhere on the board
/SMPS_PS: TP4.1; also elsewhere on the board
/SWCLK: TP8.1; also elsewhere on the board
/SWDIO: TP9.1; also elsewhere on the board
/USB_CONN_DM: TP2.1; also elsewhere on the board
/USB_CONN_DP: TP3.1; also elsewhere on the board
DVDD: TP7.1; also elsewhere on the board
GND: J4.3, J4.8, J4.13, J4.18, J4.23, J4.28, J4.33, J4.38, TP1.1, TP10.1; also elsewhere on the board
VBUS: J4.40; also elsewhere on the board
VSYS: J4.39; also elsewhere on the board

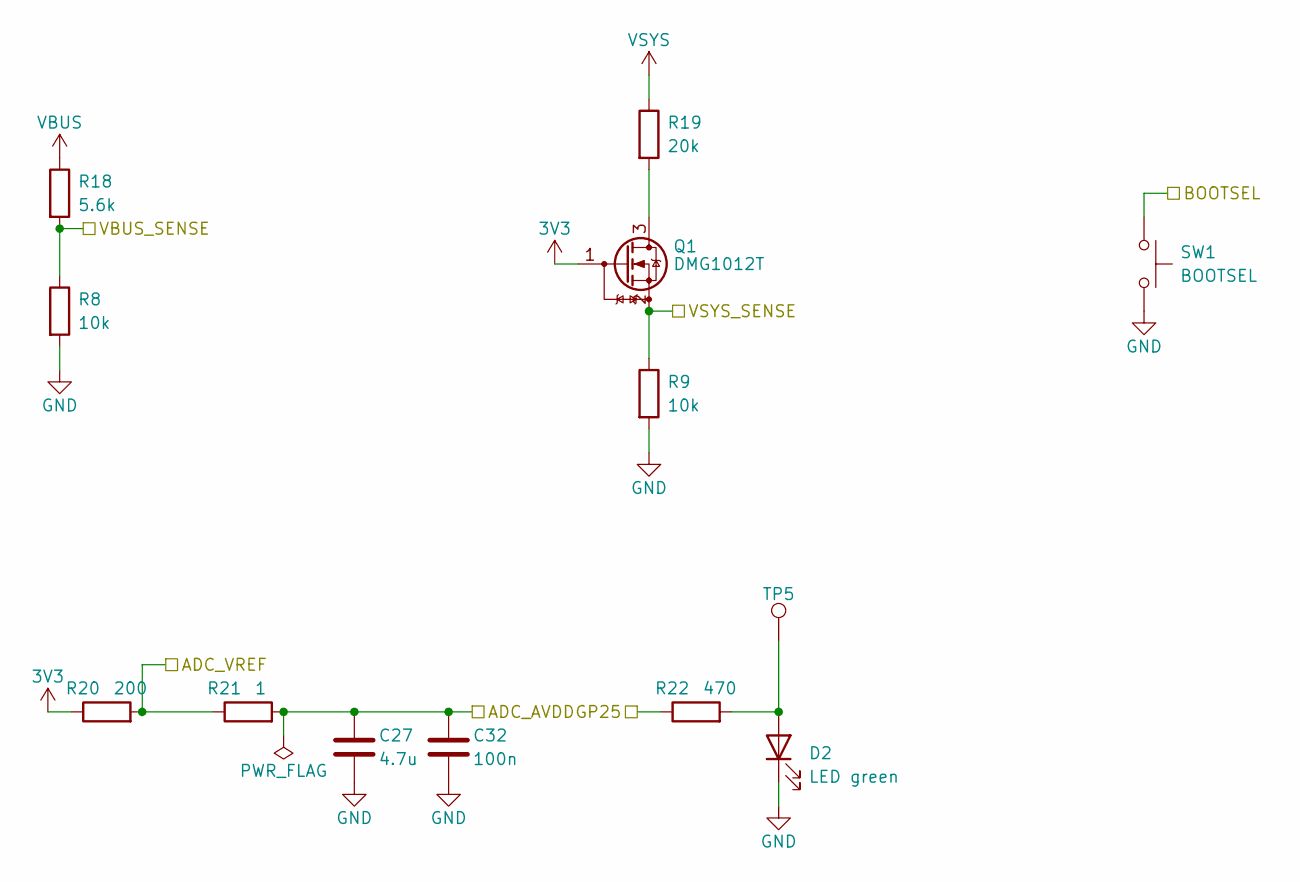
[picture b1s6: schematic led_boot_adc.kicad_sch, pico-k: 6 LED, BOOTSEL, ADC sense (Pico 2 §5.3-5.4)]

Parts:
C27: 4.7u; C_0402_1005Metric; MPN TDK105CBJ475MV-F
C32: 100n; C_0402_1005Metric; MPN CL05B104KO5NNNC
D2: LED green; LED_0805_2012Metric; MPN KT-0805G
Q1: DMG1012T; SOT-523; MPN DMG1012T-7
R8, R9: 10k; R_0402_1005Metric; MPN 0402WGF1002TCE
R18: 5.6k; R_0402_1005Metric; MPN 0402WGF5601TCE
R19: 20k; R_0402_1005Metric; MPN 0402WGF2002TCE
R20: 200; R_0402_1005Metric; MPN 0402WGF2000TCE
R21: 1; R_0402_1005Metric; MPN 0402WGF100KTCE
R22: 470; R_0402_1005Metric; MPN 0402WGF4700TCE
SW1: BOOTSEL; SW_Push_1P1T_XKB_TS-1187A; MPN TS-1187A-B-A-B
TP5: TestPoint; TestPoint_Pico2_1.5x1.5mm

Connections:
3V3: Q1.1 (G), R20.1; also elsewhere on the board
/ADC_AVDD: C27.1, C32.1, R21.2; also elsewhere on the board
/ADC_VREF: R20.2, R21.1; also elsewhere on the board
/BOOTSEL: SW1.1; also elsewhere on the board
/GP25: R22.1; also elsewhere on the board
/VBUS_SENSE: R8.1, R18.2; also elsewhere on the board
/VSYS_SENSE: Q1.2 (S), R9.1; also elsewhere on the board
GND: C27.2, C32.2, D2.1 (K), R8.2, R9.2, SW1.2; also elsewhere on the board
unnamed: D2.2 (A), R22.2, TP5.1
unnamed: Q1.3 (D), R19.2
VBUS: R18.1; also elsewhere on the board
VSYS: R19.1; also elsewhere on the board

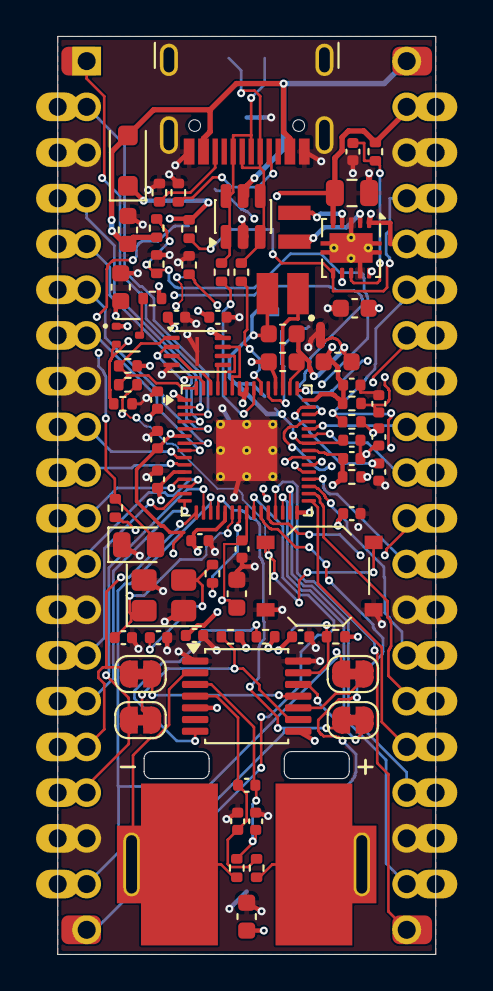
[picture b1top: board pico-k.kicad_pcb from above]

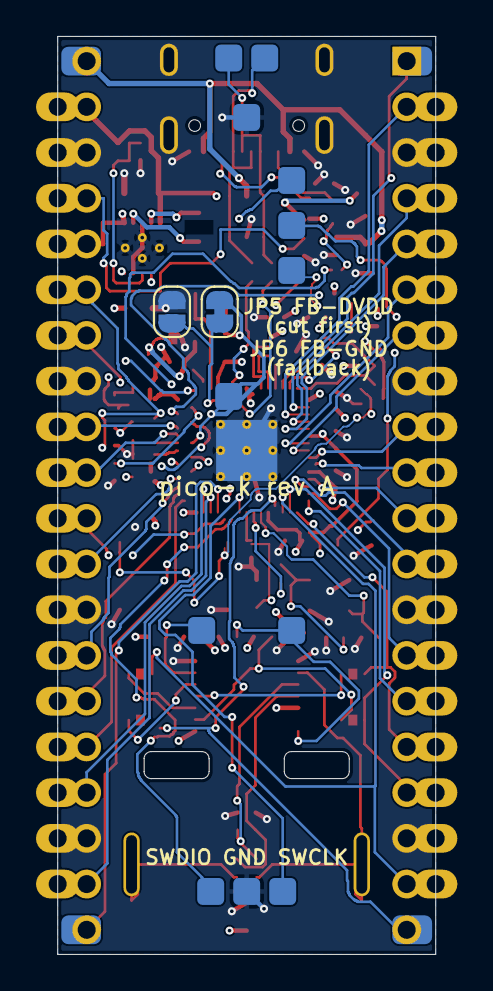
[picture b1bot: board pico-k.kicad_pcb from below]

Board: 4 copper layers, 21.0 x 51.0 mm, 89 parts (14 on the bottom side), 76 nets.

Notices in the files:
README.md:
License: CERN-OHL-P-2.0
